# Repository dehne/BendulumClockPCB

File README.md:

# Bendulum Clock Shield

Bendulum Clock PCB Copyright 2014 by D. L. Ehnebuske  
License terms: [Creative Commons Attribution-ShareAlike 3.0 United States (CC BY-SA 3.0 US)]
(http://creativecommons.org/licenses/by-sa/3.0/us/ "CC BY-SA 3.0 US")

This is drop-in replacement for the protoboard used in the initial implementation of my bendulum 
clock. It functions as an Adruino shield implementing the hardware interface between the Arduino Uno
that drives a bendulum clock and the rest of the bendulum clock. Its shape is not that of a 
traditional Arduino shield.

Note that this board was only designed, not built. The BendulumClockShield implements same 
functionality in a traditional Arduino shield and has been tested.

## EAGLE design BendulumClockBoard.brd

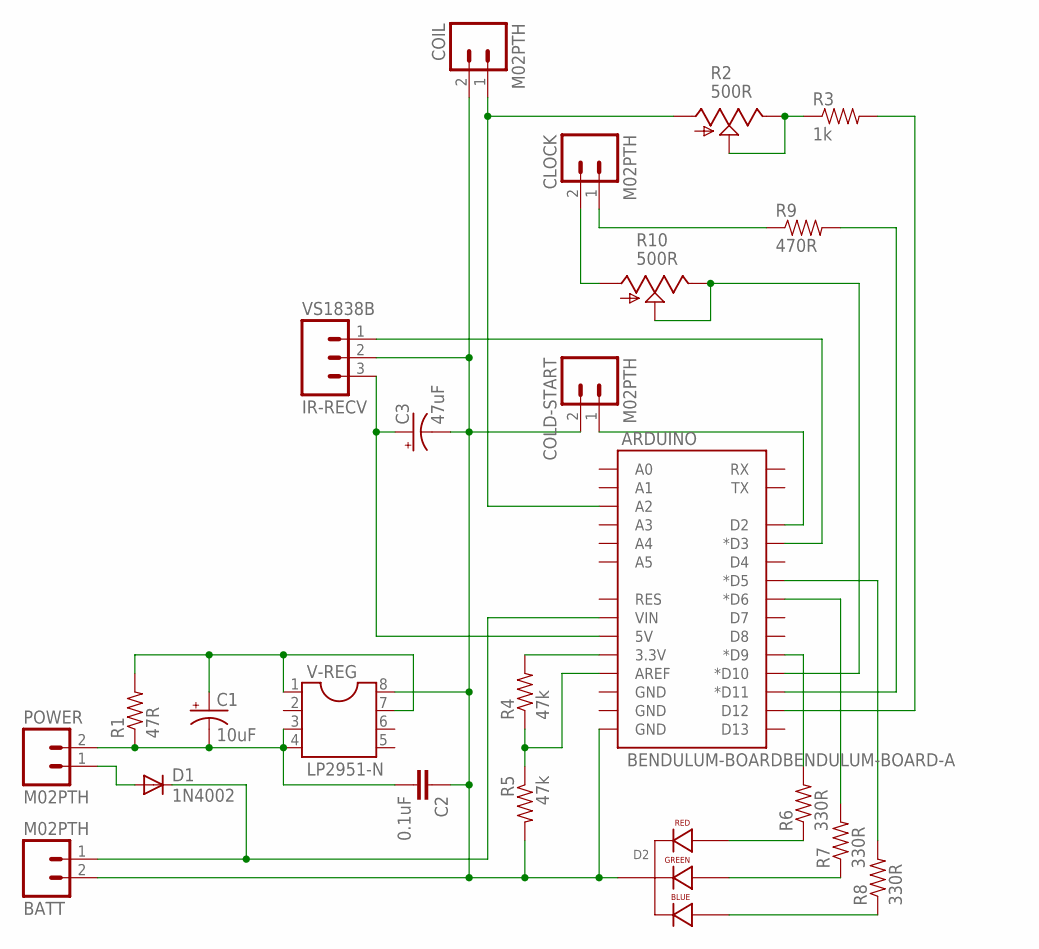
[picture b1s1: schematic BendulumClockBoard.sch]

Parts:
ARDUINO: BENDULUM-BOARDBENDULUM-BOARD-A; BENDULUM-BOARD
BATT: M02PTH; 1X02
C1: 10uF; CPOL-RADIAL-10UF-25V
C2: 0.1uF; CAP-PTH-SMALL
C3: 47uF; CPOL-RADIAL-10UF-25V
CLOCK: M02PTH; 1X02
COIL: M02PTH; 1X02
COLD-START: M02PTH; 1X02
D1: 1N4002; DIODE-1N4001-KIT
D2: LED-RGB-CC-THRUDIFFUSE; LED-RGB-THRU
IR-RECV: VS1838B; 1X03
POWER: M02PTH; 1X02
R1: 47R; AXIAL-0.4
R2, R10: 500R; S64Y
R3: 1k; AXIAL-0.4
R4, R5: 47k; AXIAL-0.4
R6, R7, R8: 330R; AXIAL-0.4
R9: 470R; AXIAL-0.4
V-REG: LP2951-N; SOCKET-08

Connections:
GND: ARDUINO.GND@0 (GND), BATT.2, C2.1, C3.2 (-), COIL.2, COLD-START.2, D2.2 (CATHODE), IR-RECV.2, R5.P$2 (2), V-REG.8 (INPUT)
unnamed: D1.A, POWER.1
unnamed: ARDUINO.VIN, BATT.1, D1.C
unnamed: C1.2 (-), C2.2, POWER.2, R1.P$1 (1), V-REG.3 (SHUTDOWN), V-REG.4 (GND)
unnamed: C1.1 (+), R1.P$2 (2), V-REG.1 (OUTPUT), V-REG.7 (FEEDBACK)
unnamed: ARDUINO.D9 (*D9), R6.P$2 (2)
unnamed: ARDUINO.A2, COIL.1, R2.A
unnamed: ARDUINO.3.3V, R4.P$2 (2)
unnamed: ARDUINO.D12, R3.P$2 (2)
unnamed: R2.E, R2.S, R3.P$1 (1)
unnamed: ARDUINO.D2, COLD-START.1
unnamed: ARDUINO.AREF, R4.P$1 (1), R5.P$1 (1)
unnamed: ARDUINO.D6 (*D6), R7.P$2 (2)
unnamed: ARDUINO.D5 (*D5), R8.P$2 (2)
unnamed: ARDUINO.D3 (*D3), IR-RECV.1
unnamed: ARDUINO.5V, C3.1 (+), IR-RECV.3
unnamed: D2.1 (RED_ANODE), R6.P$1 (1)
unnamed: D2.3 (GREEN_ANODE), R7.P$1 (1)
unnamed: D2.4 (BLUE_ANODE), R8.P$1 (1)
unnamed: CLOCK.2, R10.A
unnamed: ARDUINO.D10 (*D10), R10.E, R10.S
unnamed: CLOCK.1, R9.P$1 (1)
unnamed: ARDUINO.D11 (*D11), R9.P$2 (2)

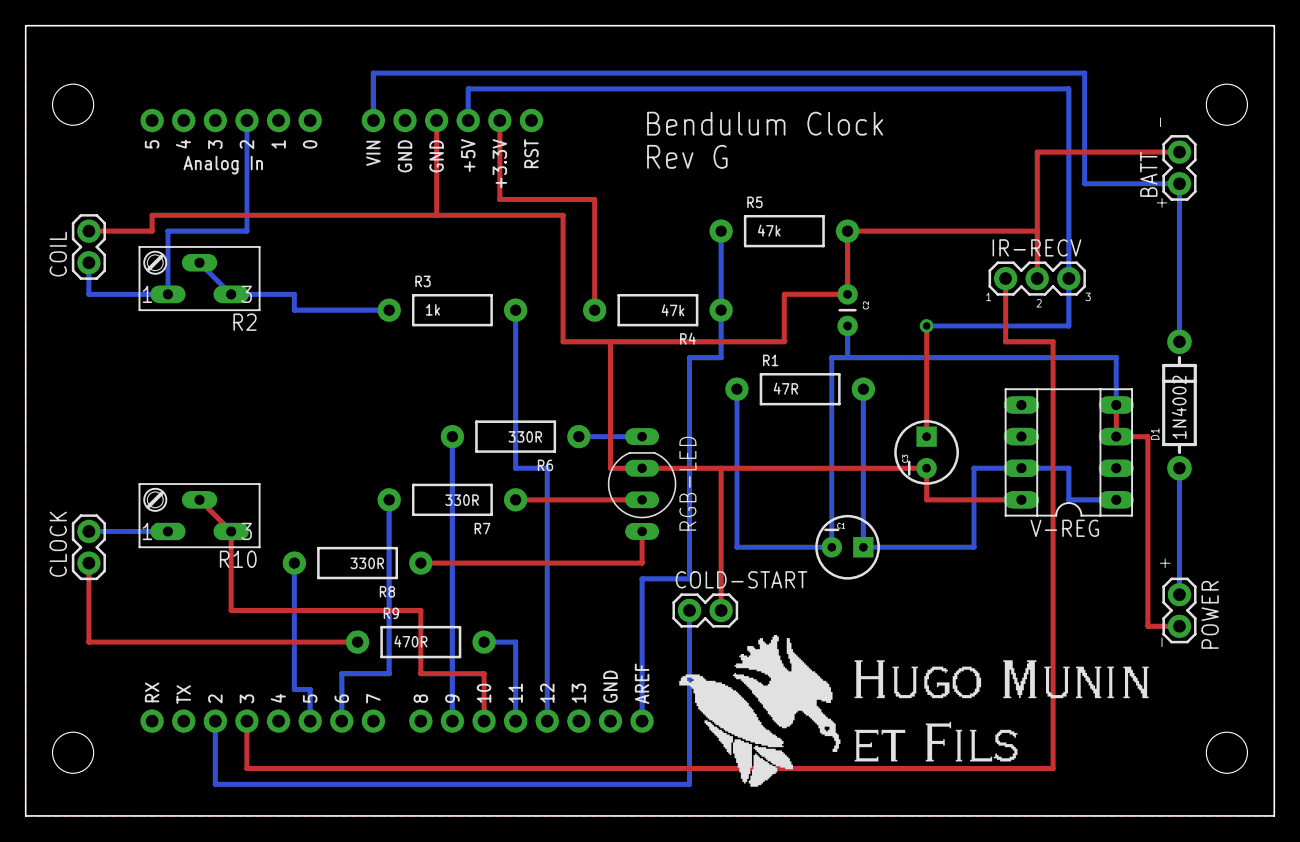
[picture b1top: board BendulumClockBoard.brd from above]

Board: 2 copper layers, 100.3 x 63.5 mm, 23 parts (0 on the bottom side), 23 nets.

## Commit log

2014-03-01 origin
    Initial commit
2014-04-25 Documentation update
    Explain relationship to BendulumClockSheild

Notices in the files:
parts and their libraries:
SparkFun-Connectors: Licensing: CC v3.0 Share-Alike You are welcome to use this library for commercial purposes.
